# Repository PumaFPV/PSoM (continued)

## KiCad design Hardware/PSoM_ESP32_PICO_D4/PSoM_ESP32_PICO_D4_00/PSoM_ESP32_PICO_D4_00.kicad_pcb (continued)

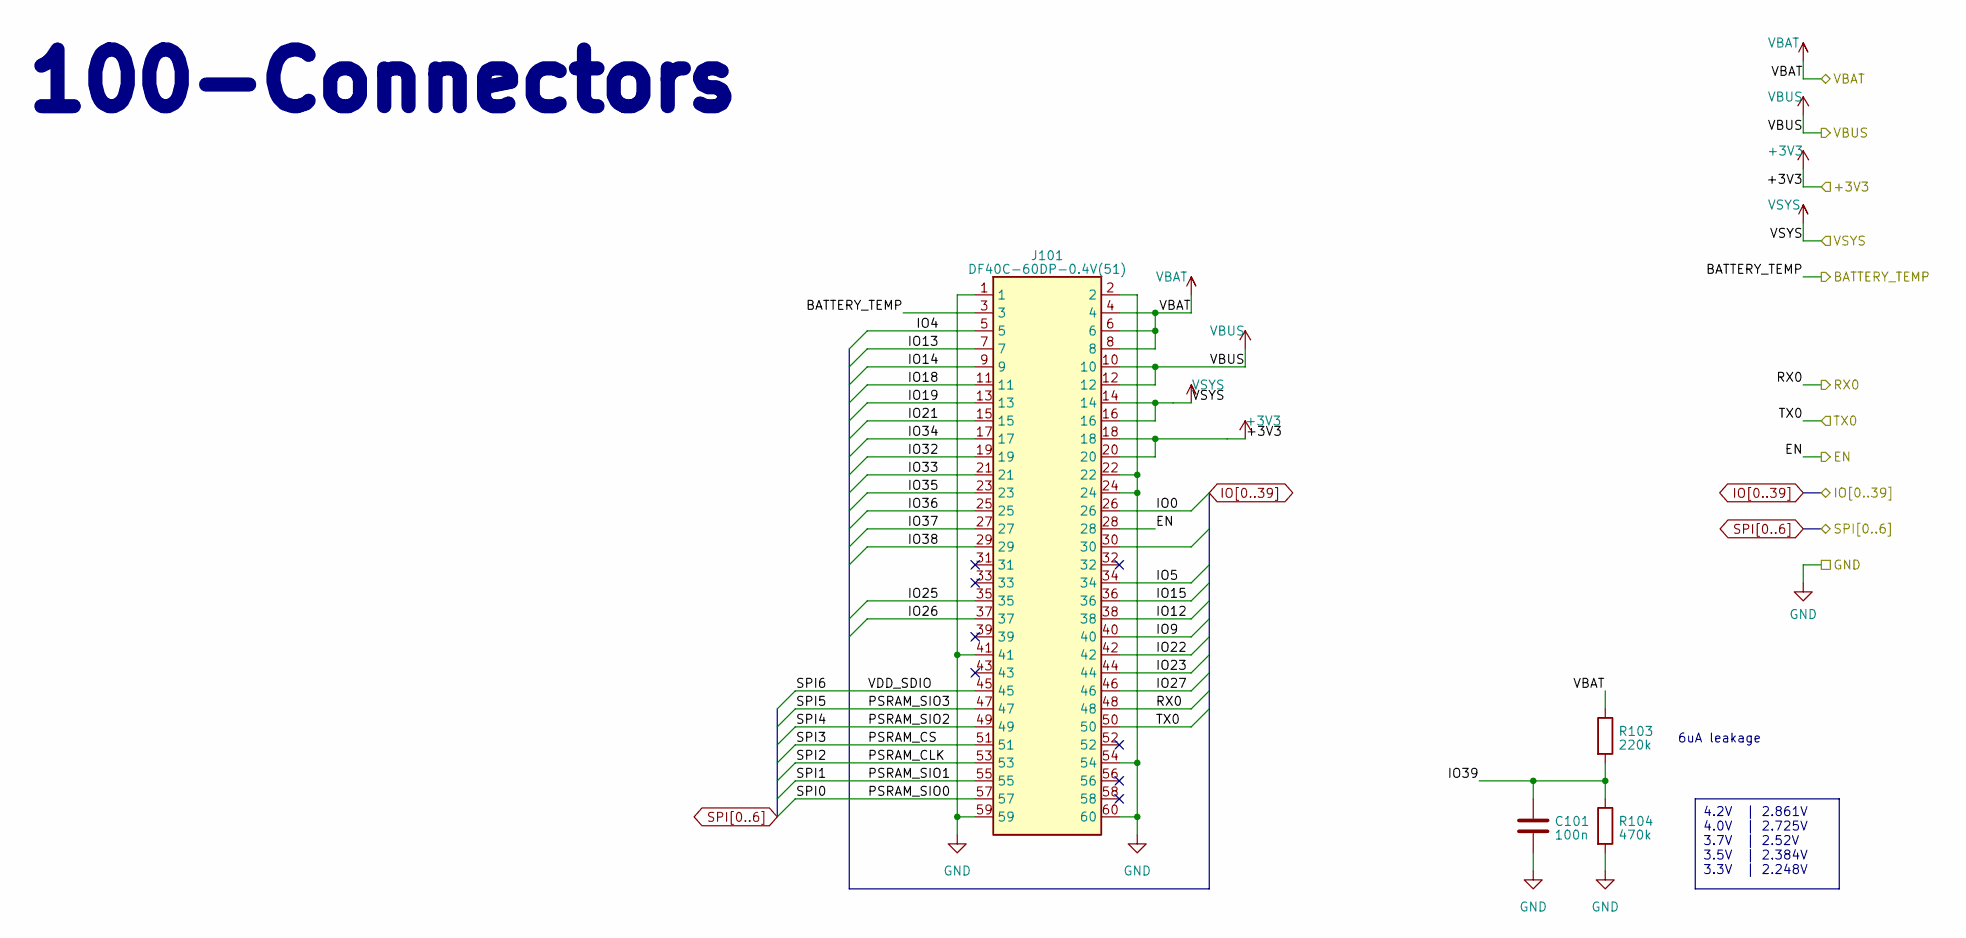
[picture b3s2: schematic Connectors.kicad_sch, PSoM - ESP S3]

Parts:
C101: 100n; C_0201_0603Metric
J101: DF40C-60DP-0.4V(51)
R103: 220k; R_0201_0603Metric
R104: 470k; R_0201_0603Metric

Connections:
+3V3: J101.18, J101.20; also elsewhere on the board
/100_Connectors/BATTERY_TEMP: J101.3; also elsewhere on the board
/100_Connectors/EN: J101.28; also elsewhere on the board
/100_Connectors/RX0: J101.48; also elsewhere on the board
/100_Connectors/TX0: J101.50; also elsewhere on the board
/VBAT: J101.4, J101.6, J101.8, R103.1; also elsewhere on the board
/VSYS: J101.14, J101.16; also elsewhere on the board
GND: C101.2, J101.1, J101.2, J101.22, J101.24, J101.41, J101.54, J101.59, J101.60, R104.2; also elsewhere on the board
IO0: J101.26; also elsewhere on the board
IO4: J101.5; also elsewhere on the board
IO5: J101.34; also elsewhere on the board
IO9: J101.40; also elsewhere on the board
IO12: J101.38; also elsewhere on the board
IO13: J101.7; also elsewhere on the board
IO14: J101.9; also elsewhere on the board
IO15: J101.36; also elsewhere on the board
IO18: J101.11; also elsewhere on the board
IO19: J101.13; also elsewhere on the board
IO21: J101.15; also elsewhere on the board
IO22: J101.42; also elsewhere on the board
IO23: J101.44; also elsewhere on the board
IO25: J101.35; also elsewhere on the board
IO26: J101.37; also elsewhere on the board
IO27: J101.46; also elsewhere on the board
IO32: J101.19; also elsewhere on the board
IO33: J101.21; also elsewhere on the board
IO34: J101.17; also elsewhere on the board
IO35: J101.23; also elsewhere on the board
IO36: J101.25; also elsewhere on the board
IO37: J101.27; also elsewhere on the board
IO38: J101.29; also elsewhere on the board
IO39: C101.1, R103.2, R104.1; also elsewhere on the board
SPI0: J101.57; also elsewhere on the board
SPI1: J101.55; also elsewhere on the board
SPI2: J101.53; also elsewhere on the board
SPI3: J101.51; also elsewhere on the board
SPI4: J101.49; also elsewhere on the board
SPI5: J101.47; also elsewhere on the board
SPI6: J101.45; also elsewhere on the board
VBUS: J101.10, J101.12; also elsewhere on the board

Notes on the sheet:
4.2V | 2.861V 4.0V | 2.725V 3.7V | 2.52V 3.5V | 2.384V 3.3V | 2.248V
100-Connectors
6uA leakage

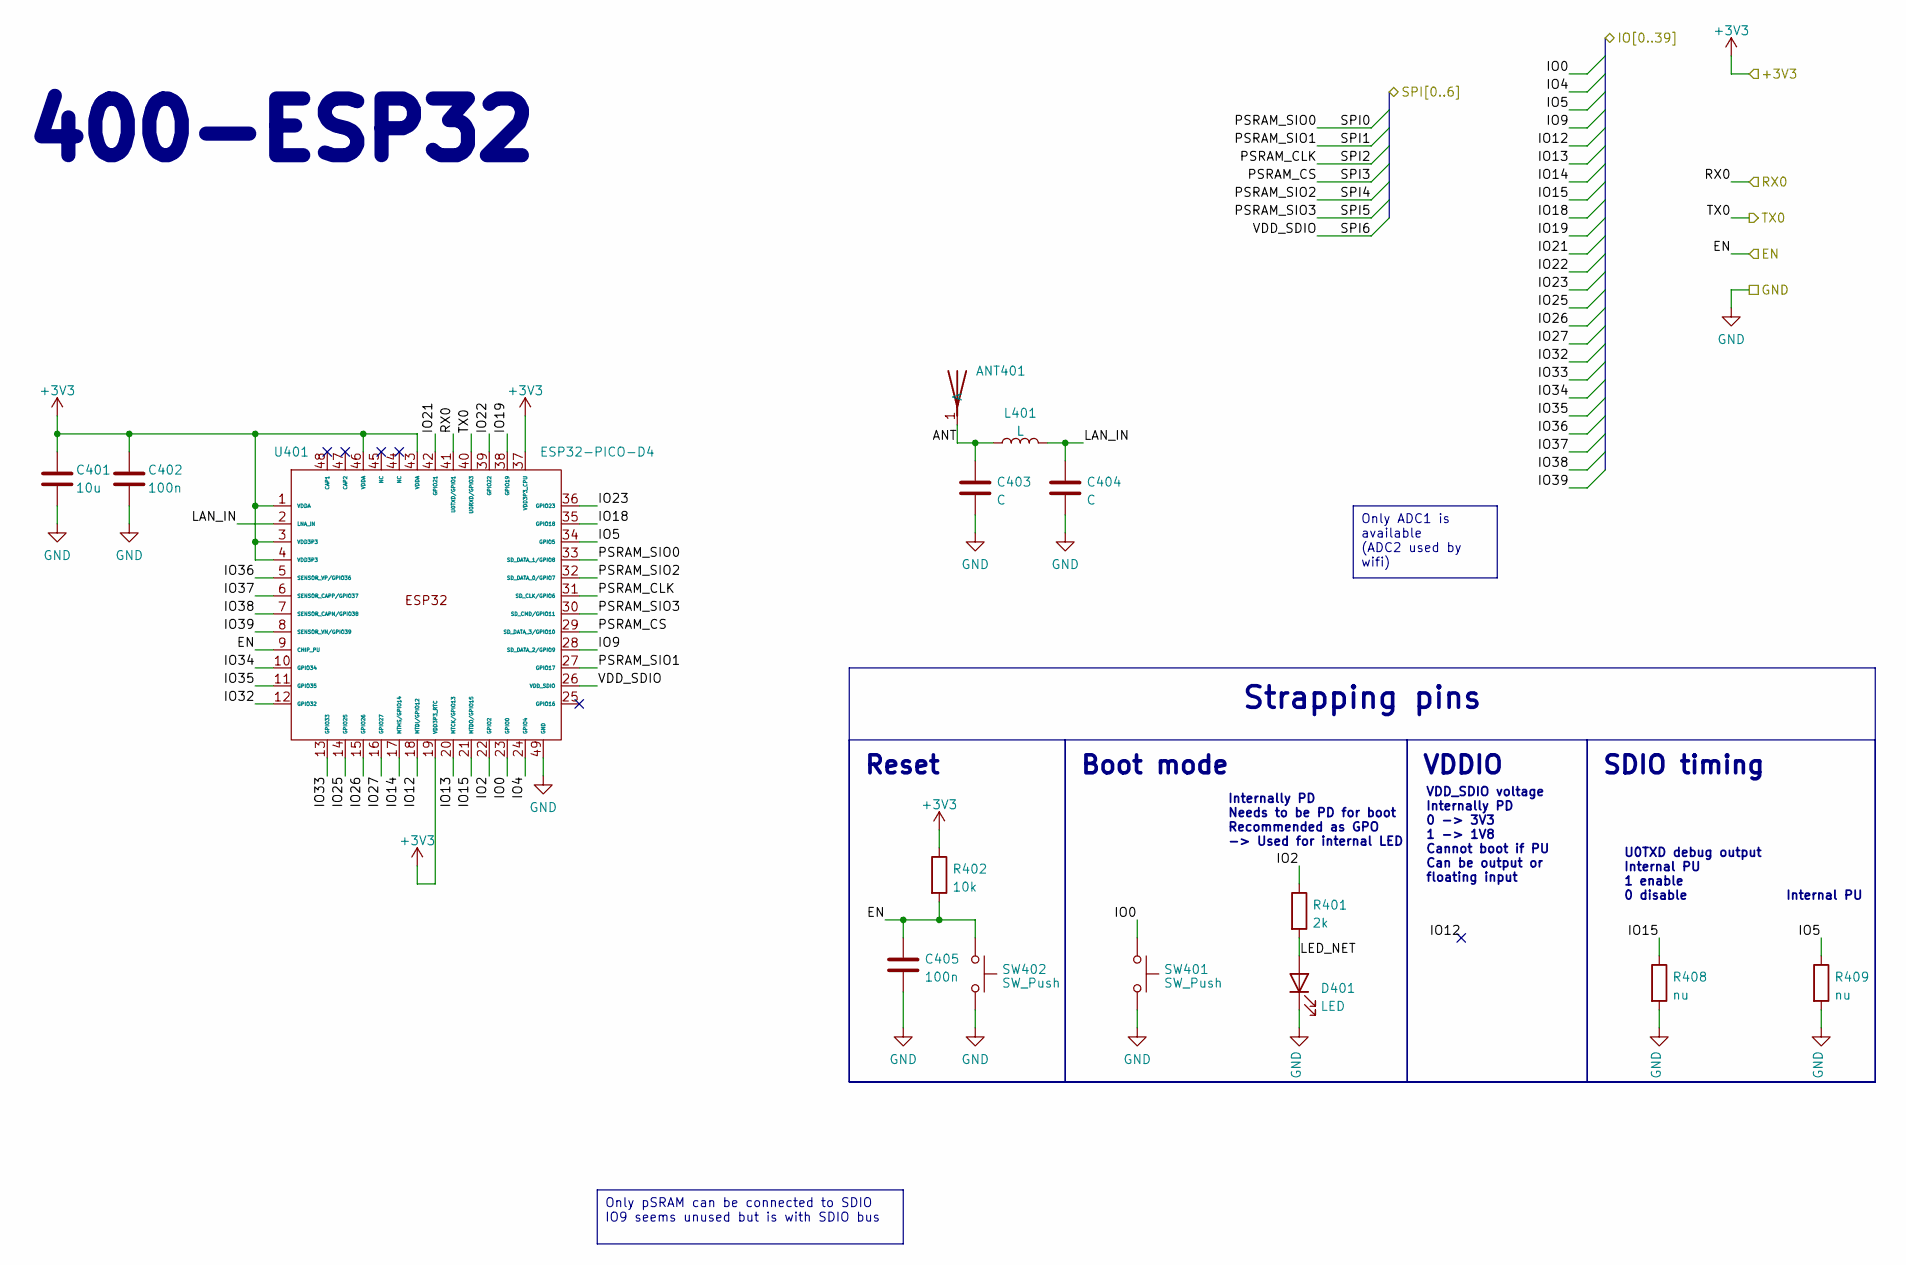
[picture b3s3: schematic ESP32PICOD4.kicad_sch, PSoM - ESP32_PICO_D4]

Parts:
ANT401: 2450AT18A100E; ANTC3216X140N; Mouser Part Number 609-2450AT18A100E
C401: 10u; C_0603_1608Metric
C402, C405: 100n; C_0201_0603Metric
C403, C404: C; C_0201_0603Metric
D401: LED; LED_0402_1005Metric
L401: L; L_0201_0603Metric
R401: 2k; R_0402_1005Metric
R402: 10k; R_0201_0603Metric
R408, R409: nu; R_0201_0603Metric
SW401, SW402: SW_Push; B3U-1000P
U401: ESP32-PICO-D4; ESP32-PICO-D4_1; Mouser Part Number 356-ESP32-PICO-D4

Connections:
+3V3: C401.1, C402.1, R402.1, U401.1 (VDDA), U401.3 (VDD3P3), U401.4 (VDD3P3), U401.19 (VDD3P3_RTC), U401.37 (VDD3P3_CPU), U401.43 (VDDA), U401.46 (VDDA); also elsewhere on the board
/100_Connectors/EN: C405.1, R402.2, SW402.1, U401.9 (CHIP_PU); also elsewhere on the board
/100_Connectors/RX0: U401.41 (U0TXD/GPIO1); also elsewhere on the board
/100_Connectors/TX0: U401.40 (U0RXD/GPIO3); also elsewhere on the board
/400_ESP32/ANT: ANT401.1 (A), C403.1, L401.1
/400_ESP32/LAN_IN: C404.1, L401.2, U401.2 (LNA_IN)
/400_ESP32/LED_NET: D401.2 (A), R401.2
GND: C401.2, C402.2, C403.2, C404.2, C405.2, D401.1 (K), R408.2, R409.2, SW401.2, SW402.2, U401.49 (GND); also elsewhere on the board
IO0: SW401.1, U401.23 (GPIO0); also elsewhere on the board
IO2: R401.1, U401.22 (GPIO2)
IO4: U401.24 (GPIO4); also elsewhere on the board
IO5: R409.1, U401.34 (GPIO5); also elsewhere on the board
IO9: U401.28 (SD_DATA_2/GPIO9); also elsewhere on the board
IO12: U401.18 (MTDI/GPIO12); also elsewhere on the board
IO13: U401.20 (MTCK/GPIO13); also elsewhere on the board
IO14: U401.17 (MTMS/GPIO14); also elsewhere on the board
IO15: R408.1, U401.21 (MTDO/GPIO15); also elsewhere on the board
IO18: U401.35 (GPIO18); also elsewhere on the board
IO19: U401.38 (GPIO19); also elsewhere on the board
IO21: U401.42 (GPIO21); also elsewhere on the board
IO22: U401.39 (GPIO22); also elsewhere on the board
IO23: U401.36 (GPIO23); also elsewhere on the board
IO25: U401.14 (GPIO25); also elsewhere on the board
IO26: U401.15 (GPIO26); also elsewhere on the board
IO27: U401.16 (GPIO27); also elsewhere on the board
IO32: U401.12 (GPIO32); also elsewhere on the board
IO33: U401.13 (GPIO33); also elsewhere on the board
IO34: U401.10 (GPIO34); also elsewhere on the board
IO35: U401.11 (GPIO35); also elsewhere on the board
IO36: U401.5 (SENSOR_VP/GPIO36); also elsewhere on the board
IO37: U401.6 (SENSOR_CAPP/GPIO37); also elsewhere on the board
IO38: U401.7 (SENSOR_CAPN/GPIO38); also elsewhere on the board
IO39: U401.8 (SENSOR_VN/GPIO39); also elsewhere on the board
SPI0: U401.33 (SD_DATA_1/GPIO8); also elsewhere on the board
SPI1: U401.27 (GPIO17); also elsewhere on the board
SPI2: U401.31 (SD_CLK/GPIO6); also elsewhere on the board
SPI3: U401.29 (SD_DATA_3/GPIO10); also elsewhere on the board
SPI4: U401.32 (SD_DATA_0/GPIO7); also elsewhere on the board
SPI5: U401.30 (SD_CMD/GPIO11); also elsewhere on the board
SPI6: U401.26 (VDD_SDIO); also elsewhere on the board

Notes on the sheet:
Only pSRAM can be connected to SDIO IO9 seems unused but is with SDIO bus
Reset
SDIO timing
VDDIO
Boot mode
Strapping pins
Only ADC1 is available (ADC2 used by wifi)
Internally PD Needs to be PD for boot Recommended as GPO -> Used for internal LED
Internal PU
400-ESP32
VDD_SDIO voltage Internally PD 0 -> 3V3 1 -> 1V8 Cannot boot if PU Can be output or floating input
U0TXD debug output Internal PU 1 enable 0 disable

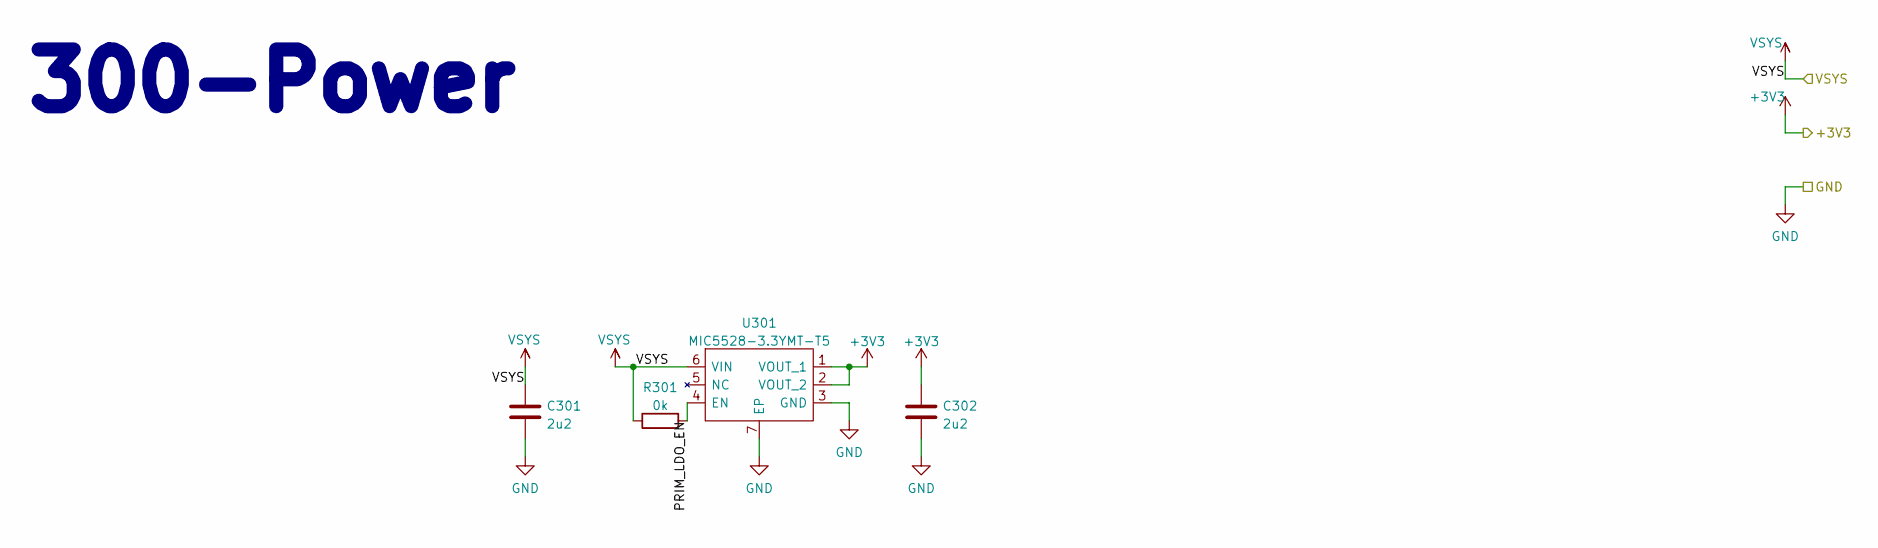
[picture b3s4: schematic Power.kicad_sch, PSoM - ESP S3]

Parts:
C301, C302: 2u2; C_0603_1608Metric
R301: 0k; R_0201_0603Metric
U301: MIC5528-3.3YMT-T5; SON40P120X120X60-7N-D; Mouser Part Number 998-MIC5528-3.3YMTT5

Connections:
+3V3: C302.1, U301.1 (VOUT_1), U301.2 (VOUT_2); also elsewhere on the board
/300_Power/PRIM_LDO_EN: R301.2, U301.4 (EN)
/VSYS: C301.1, R301.1, U301.6 (VIN); also elsewhere on the board
GND: C301.2, C302.2, U301.3 (GND), U301.7 (EP); also elsewhere on the board

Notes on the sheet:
300-Power

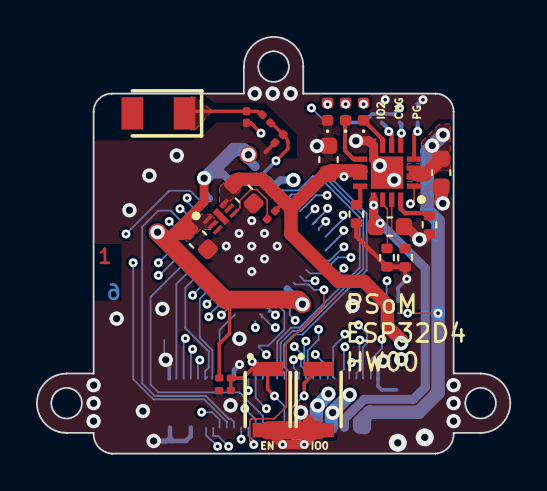
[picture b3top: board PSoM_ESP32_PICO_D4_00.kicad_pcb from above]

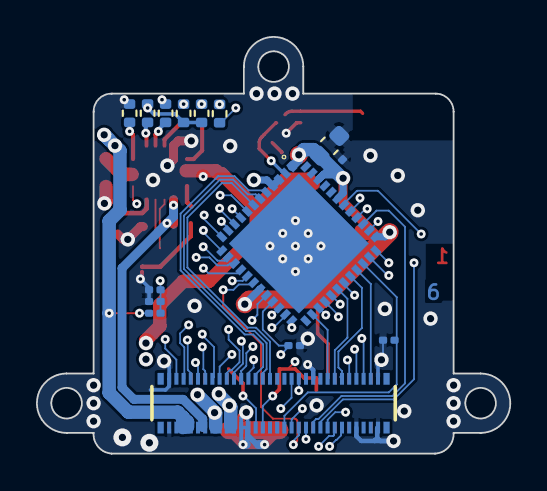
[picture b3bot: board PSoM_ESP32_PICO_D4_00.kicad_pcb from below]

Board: 6 copper layers, 26.3 x 23.2 mm, 38 parts (15 on the bottom side), 56 nets.

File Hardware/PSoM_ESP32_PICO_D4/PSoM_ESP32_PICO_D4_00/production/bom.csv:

Designator,Footprint,Quantity,Value,LCSC Part #
ANT401,ANTC3216X140N,1,2450AT18A100E,
"C101, C402, C405",0201,3,100n,
"C201, C203",0603,2,4u7,
C202,0603,1,1u,
"C301, C302",0603,2,2u2,
C401,0603,1,10u,
"C403, C404",0201,2,C,
"D201, D202, D401",0402,3,LED,
J101,DF40C-60DP-0.4V(51),1,DF40C-60DP-0.4V(51),
L401,0201,1,L,
"R1, R2",0402,2,R,
R103,0201,1,220k,
R104,0201,1,470k,
R201,0402,1,0,
R202,0402,1,36k5,
R203,0402,1,590,
R204,0402,1,1k1,
"R205, R206",0402,2,1k5,
R207,0402,1,100k,
R301,0201,1,0k,
R401,0402,1,2k,
R402,0201,1,10k,
"R408, R409",0201,2,nu,
"SW401, SW402",B3U-1000P,2,SW_Push,
U201,QFN50P300X300X100-17N-D,1,BQ24075RGTR,
U301,SON40P120X120X60-7N-D,1,MIC5528-3.3YMT-T5,
U401,ESP32-PICO-D4_1,1,ESP32-PICO-D4,

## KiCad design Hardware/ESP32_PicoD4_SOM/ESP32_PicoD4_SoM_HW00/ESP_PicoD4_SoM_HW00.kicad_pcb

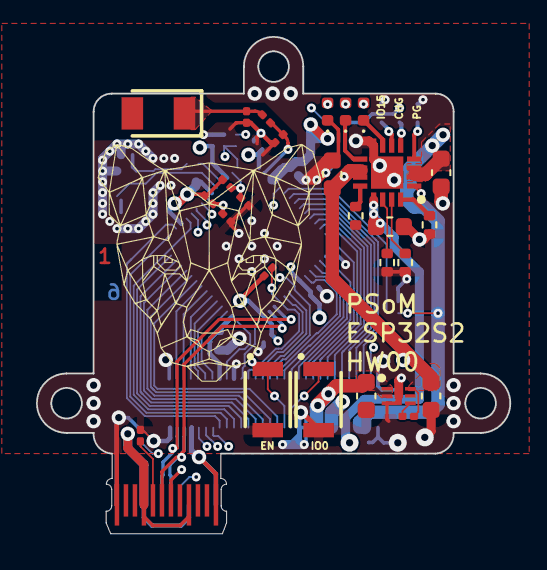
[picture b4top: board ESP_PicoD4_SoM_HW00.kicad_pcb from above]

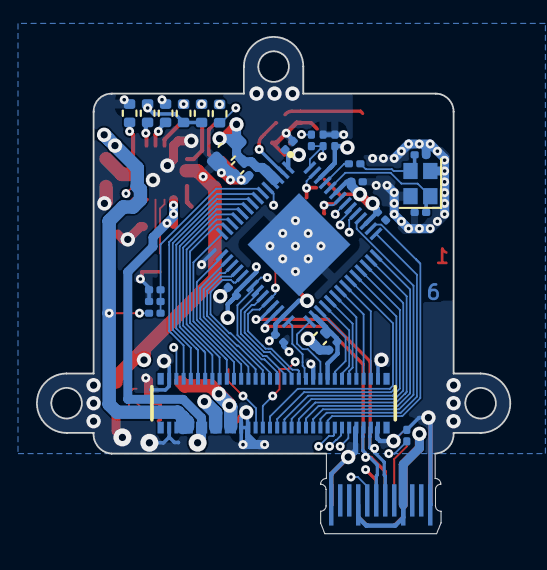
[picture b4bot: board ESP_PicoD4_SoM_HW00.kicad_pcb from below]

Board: 6 copper layers, 26.3 x 27.6 mm, 57 parts (29 on the bottom side), 71 nets.

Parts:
ANT401: 2450AT18A100E; ANTC3216X140N
C101, C403, C404, C405, C408, C411, C412, C414, C415, C416: 100n; C_0201_0603Metric
C201, C203: 4u7; C_0603_1608Metric
C202: 1u; C_0603_1608Metric
C301, C302: 2u2; C_0603_1608Metric
C401, C402: 15p; C_0201_0603Metric
C406, C407: C; C_0201_0603Metric
C409: 10u; C_0603_1608Metric
C410, C413: 1u; C_0402_1005Metric
D201, D202, D401: LED; LED_0402_1005Metric
J101: DF40C-60DP-0.4V(51)
J102: Bare PCB USB C; usb-c-pcb
L401: L; L_0201_0603Metric
R1, R2: R; R_0402_1005Metric
R101, R102: 5.1k; R_0201_0603Metric
R103: 220k; R_0201_0603Metric
R104: 470k; R_0201_0603Metric
R201: 0; R_0402_1005Metric
R202: 36k5; R_0402_1005Metric
R203: 590; R_0402_1005Metric
R204: 1k1; R_0402_1005Metric
R205, R206: 1k5; R_0402_1005Metric
R207: 100k; R_0402_1005Metric
R301: 0k; R_0201_0603Metric
R401: 0; R_0201_0603Metric
R402: 2k; R_0402_1005Metric
R403, R404: 10k; R_0201_0603Metric
R405, R406, R407, R408: nu; R_0201_0603Metric
SW401, SW402: SW_Push; B3U-1000P
U201: BQ24075RGTR; QFN50P300X300X100-17N-D
U301: MIC5528-3.3YMT-T5; SON40P120X120X60-7N-D
U401: ESP32-S2FH4; QFN40P700X700X90-57N-D
Y601: Crystal_GND24_Small; Crystal_SMD_2016-4Pin_2.0x1.6mm

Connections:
+3V3: C302.1, C403.1, C404.1, C405.1, C408.1, C409.1, C410.1, C411.1, C415.1, C416.1, J101.18, J101.20, R403.1, R404.1, R405.1, R406.1, U301.1 (VOUT_1), U301.2 (VOUT_2), U401.1 (VDDA_1), U401.3 (VDD3P3_1), U401.4 (VDD3P3_2), U401.20 (VDD3P3_RTC), U401.27 (VDD3P3_RTC_IO), U401.45 (VDD3P3_CPU), U401.51 (VDDA_2), U401.54 (VDDA_3)
/100_Connectors/BATTERY_TEMP: J101.3, U201.1 (TS)
/100_Connectors/CC1: J102.A5 (CC1), R102.1
/100_Connectors/CC2: J102.B5 (CC2), R101.1
/100_Connectors/D+: J101.56, J102.A6 (D+), J102.B6 (D+), U401.26 (GPIO20)
/100_Connectors/D-: J101.58, J102.A7 (D-), J102.B7 (D-), U401.25 (GPIO19)
/100_Connectors/EN: C414.1, J101.28, R403.2, SW401.1, U401.56 (CHIP_PU)
/100_Connectors/RX0: J101.48, U401.49 (U0RXD)
/100_Connectors/TX0: J101.50, U401.48 (U0TXD)
/200_1S_Charger/BQ_CE: R207.1, U201.4 (~CE)
/200_1S_Charger/BQ_CHG: D202.1 (K), U201.9 (~CHG)
/200_1S_Charger/BQ_PGOOD: D201.1 (K), U201.7 (~PGOOD)
/200_1S_Charger/EN1: R1.1, U201.6 (EN1)
/200_1S_Charger/EN2: R2.1, U201.5 (EN2)
/200_1S_Charger/ILIM: R204.2, U201.12 (ILIM)
/200_1S_Charger/ISET: R203.1, U201.16 (ISET)
/200_1S_Charger/LED_CHG: D202.2 (A), R206.2
/200_1S_Charger/LED_PG: D201.2 (A), R205.2
/200_1S_Charger/SYSOFF: R201.1, U201.15 (SYSOFF)
/200_1S_Charger/TMR: R202.1, U201.14 (TMR)
/300_Power/PRIM_LDO_EN: R301.2, U301.4 (EN)
/400_ESP32/ANT: ANT401.1 (A), C406.1, L401.1
/400_ESP32/IO45: R406.2, R408.1, U401.50 (GPIO45)
/400_ESP32/IO46: R405.2, R407.1, U401.55 (GPIO46)
/400_ESP32/LED_NET: D401.2 (A), R402.2
/400_ESP32/LNA_IN: C407.1, L401.2, U401.2 (LNA_IN)
/VBAT: C201.1, J101.4, J101.6, J101.8, R103.1, U201.2 (BAT_1), U201.3 (BAT_2)
/VSYS: C203.1, C301.1, J101.14, J101.16, R2.2, R205.1, R206.1, R301.1, U201.10 (OUT_1), U201.11 (OUT_2), U301.6 (VIN)
GND: C101.2, C201.2, C202.2, C203.2, C301.2, C302.2, C401.2, C402.2, C403.2, C404.2, C405.2, C406.2, C407.2, C408.2, C409.2, C410.2, C411.2, C412.2, C413.2, C414.2, C415.2, C416.2, D401.1 (K), J101.1, J101.2, J101.22, J101.24, J101.41, J101.54, J101.59, J101.60, J102.A1 (GND), J102.A12 (GND), J102.B1 (GND), J102.B12 (GND), R1.2, R101.2, R102.2, R104.2, R201.2, R202.2, R203.2, R204.1, R207.2, R407.2, R408.2, SW401.2, SW402.2, U201.8 (VSS), U201.17 (GND), U301.3 (GND), U301.7 (EP), U401.57 (GND), Y601.2, Y601.4
IO0: J101.26, SW402.1, U401.5 (GPIO0)
IO1: C101.1, R103.2, R104.1, U401.6 (GPIO1)
IO2: J101.5, U401.7 (GPIO2)
IO3: J101.7, U401.8 (GPIO3)
IO4: J101.9, U401.9 (GPIO4)
IO5: J101.11, U401.10 (GPIO5)
IO6: J101.13, U401.11 (GPIO6)
IO7: J101.15, U401.12 (GPIO7)
IO8: J101.17, U401.13 (GPIO8)
IO9: J101.19, U401.14 (GPIO9)
IO10: J101.21, U401.15 (GPIO10)
IO11: J101.23, U401.16 (GPIO11)
IO12: J101.25, U401.17 (GPIO12)
IO13: J101.27, U401.18 (GPIO13)
IO14: J101.29, U401.19 (GPIO14)
IO15: J101.31, R402.1, U401.21 (XTAL_32K_P)
IO16: J101.33, U401.22 (XTAL_32K_N)
IO17: J101.35, U401.23 (DAC_1)
IO18: J101.37, R404.2, U401.24 (DAC_2)
IO21: J101.39, U401.28 (GPIO21)
IO33: J101.30, U401.37 (GPIO33)
IO34: J101.32, U401.38 (GPIO34)
IO35: J101.34, U401.39 (GPIO35)
IO36: J101.36, U401.40 (GPIO36)
IO37: J101.38, U401.41 (GPIO37)
IO38: J101.40, U401.42 (GPIO38)
IO39: J101.44, U401.43 (MTCK)
IO40: J101.46, U401.44 (MTD0)
IO41: J101.42, U401.46 (MTDI)
IO42: J101.52, U401.47 (MTMS)
unnamed: C401.1, R401.1, Y601.3
unnamed: C402.1, U401.52 (XTAL_N), Y601.1
unnamed: R401.2, U401.53 (XTAL_P)
SPI0: J101.57, U401.36 (SPID)
SPI1: J101.55, U401.35 (SPIQ)
SPI2: J101.53, U401.34 (SPICLK)
SPI3: J101.51, U401.33 (SPICS0)
SPI4: J101.49, U401.32 (SPIWP)
SPI5: J101.47, U401.31 (SPIHD)
SPI6: C412.1, C413.1, J101.45, U401.30 (VDD_SPI)
SPI7: J101.43, U401.29 (SPICS1)
VBUS: C202.1, J101.10, J101.12, J102.A4 (VBUS), J102.A9 (VBUS), J102.B4 (VBUS), J102.B9 (VBUS), U201.13 (IN)

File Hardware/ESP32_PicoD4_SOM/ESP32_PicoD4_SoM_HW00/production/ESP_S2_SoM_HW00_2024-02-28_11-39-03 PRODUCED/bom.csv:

Designator,Footprint,Quantity,Value,LCSC Part #
ANT401,ANTC3216X140N,1,2450AT18A100E,
"C101, C403, C404, C405, C408, C411, C412, C414, C415, C416",0201,10,100n,
"C201, C203",0603,2,4u7,
C202,0603,1,1u,
"C301, C302",0603,2,2u2,
"C401, C402",0201,2,15p,
"C406, C407",0201,2,C,
C409,0603,1,10u,
"C410, C413",0402,2,1u,
"D201, D202, D401",0402,3,LED,
J101,DF40C-60DP-0.4V(51),1,DF40C-60DP-0.4V(51),
J102,usb-c-pcb,1,Bare PCB USB C,
L401,0201,1,L,
"R1, R2",0402,2,R,
"R101, R102",0201,2,5.1k,
R103,0201,1,220k,
R104,0201,1,470k,
R201,0402,1,0,
R202,0402,1,36k5,
R203,0402,1,590,
R204,0402,1,1k1,
"R205, R206",0402,2,1k5,
R207,0402,1,100k,
R301,0201,1,0k,
R401,0201,1,0,
R402,0402,1,2k,
"R403, R404",0201,2,10k,
"R405, R406, R407, R408",0201,4,nu,
"SW401, SW402",B3U-1000P,2,SW_Push,
U201,QFN50P300X300X100-17N-D,1,BQ24075RGTR,
U301,SON40P120X120X60-7N-D,1,MIC5528-3.3YMT-T5,
U401,QFN40P700X700X90-57N-D,1,ESP32-S2FH4,
Y601,Crystal_SMD_2016-4Pin_2.0x1.6mm,1,Crystal_GND24_Small,

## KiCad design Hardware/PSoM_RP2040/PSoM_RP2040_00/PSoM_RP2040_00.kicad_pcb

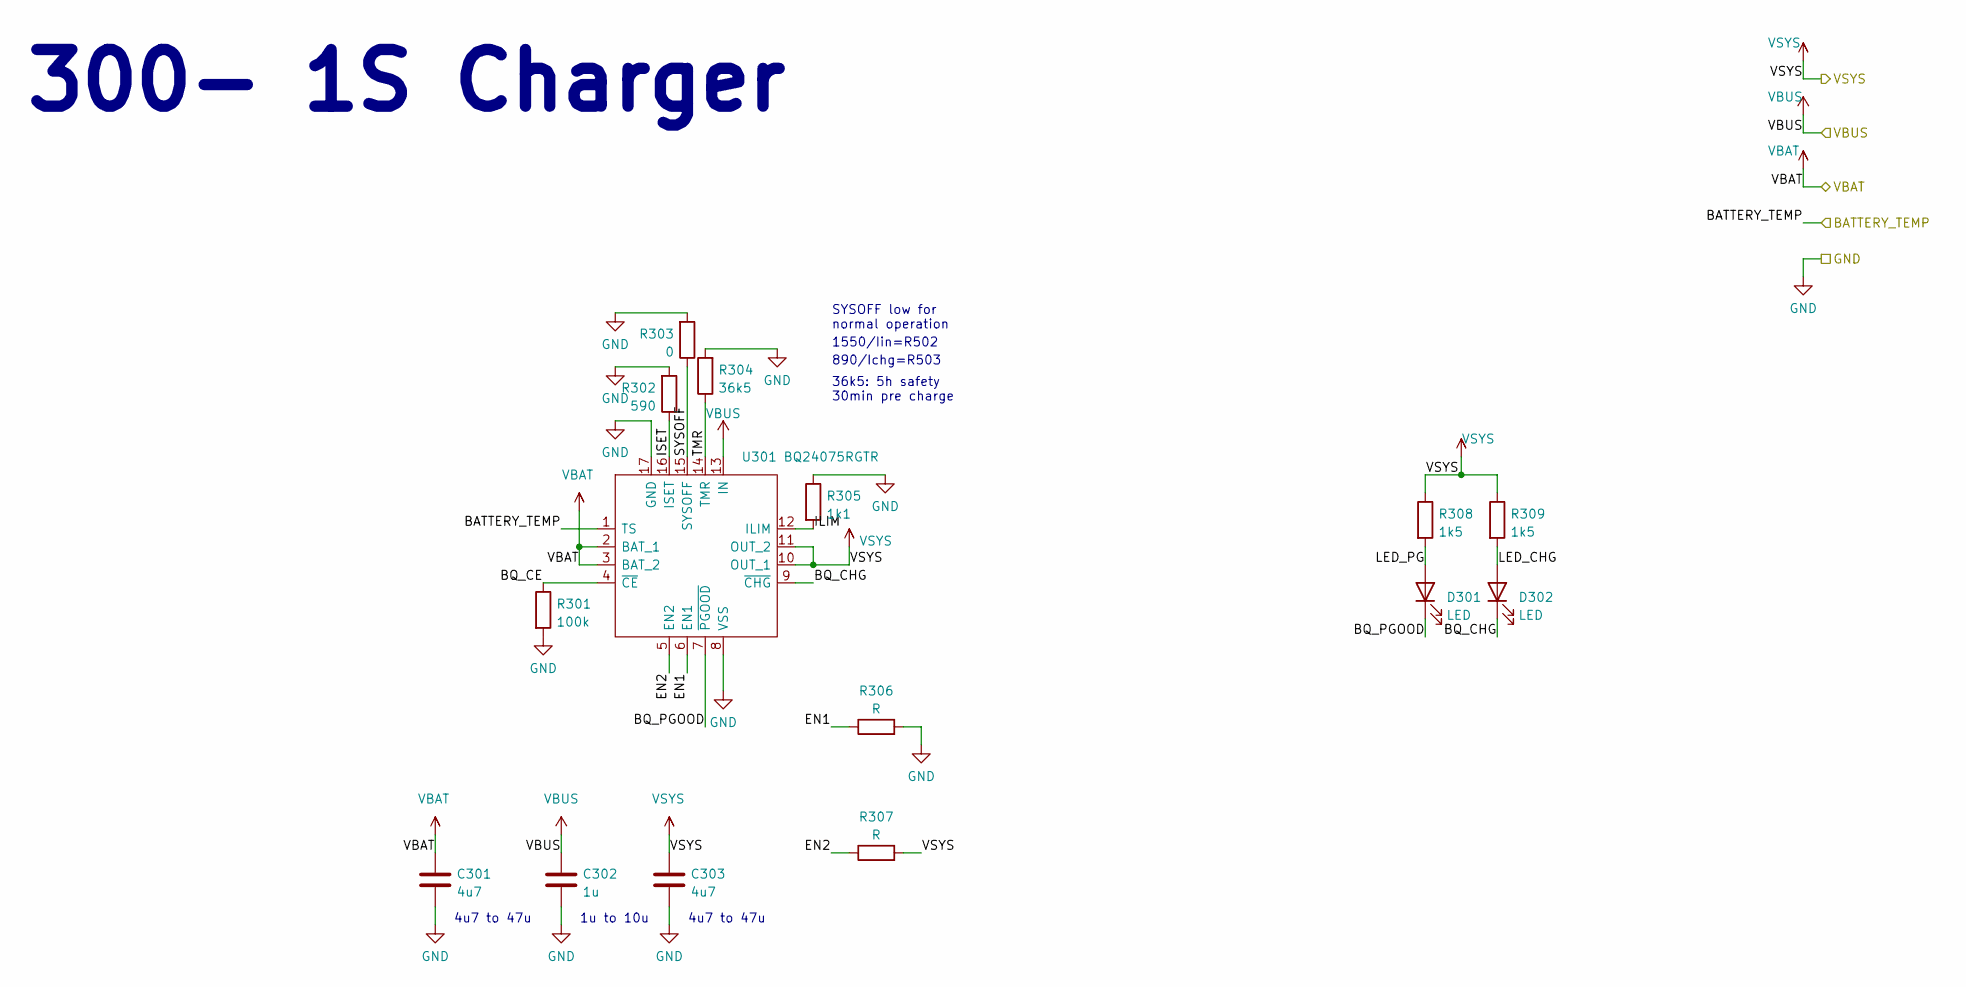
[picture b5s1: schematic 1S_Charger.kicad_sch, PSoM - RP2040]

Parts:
C301, C303: 4u7; C_0603_1608Metric
C302: 1u; C_0603_1608Metric
D301, D302: LED; LED_0402_1005Metric
R301: 100k; R_0402_1005Metric
R302: 590; R_0402_1005Metric
R303: 0; R_0402_1005Metric
R304: 36k5; R_0402_1005Metric
R305: 1k1; R_0402_1005Metric
R306, R307: R; R_0402_1005Metric
R308, R309: 1k5; R_0402_1005Metric
U301: BQ24075RGTR; QFN50P300X300X100-17N-D; Mouser Part Number 595-BQ24075RGTR

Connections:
/200_Connectors/BATTERY_TEMP: U301.1 (TS); also elsewhere on the board
/300_1S_Charger/BQ_CE: R301.1, U301.4 (~CE)
/300_1S_Charger/BQ_CHG: D302.1 (K), U301.9 (~CHG)
/300_1S_Charger/BQ_PGOOD: D301.1 (K), U301.7 (~PGOOD)
/300_1S_Charger/EN1: R306.1, U301.6 (EN1)
/300_1S_Charger/EN2: R307.1, U301.5 (EN2)
/300_1S_Charger/ILIM: R305.2, U301.12 (ILIM)
/300_1S_Charger/ISET: R302.1, U301.16 (ISET)
/300_1S_Charger/LED_CHG: D302.2 (A), R309.2
/300_1S_Charger/LED_PG: D301.2 (A), R308.2
/300_1S_Charger/SYSOFF: R303.1, U301.15 (SYSOFF)
/300_1S_Charger/TMR: R304.1, U301.14 (TMR)
/VBAT: C301.1, U301.2 (BAT_1), U301.3 (BAT_2); also elsewhere on the board
/VSYS: C303.1, R307.2, R308.1, R309.1, U301.10 (OUT_1), U301.11 (OUT_2); also elsewhere on the board
VBUS: C302.1, U301.13 (IN); also elsewhere on the board

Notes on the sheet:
890/Ichg=R503
300- 1S Charger
4u7 to 47u
1u to 10u
SYSOFF low for normal operation
36k5: 5h safety 30min pre charge
1550/Iin=R502

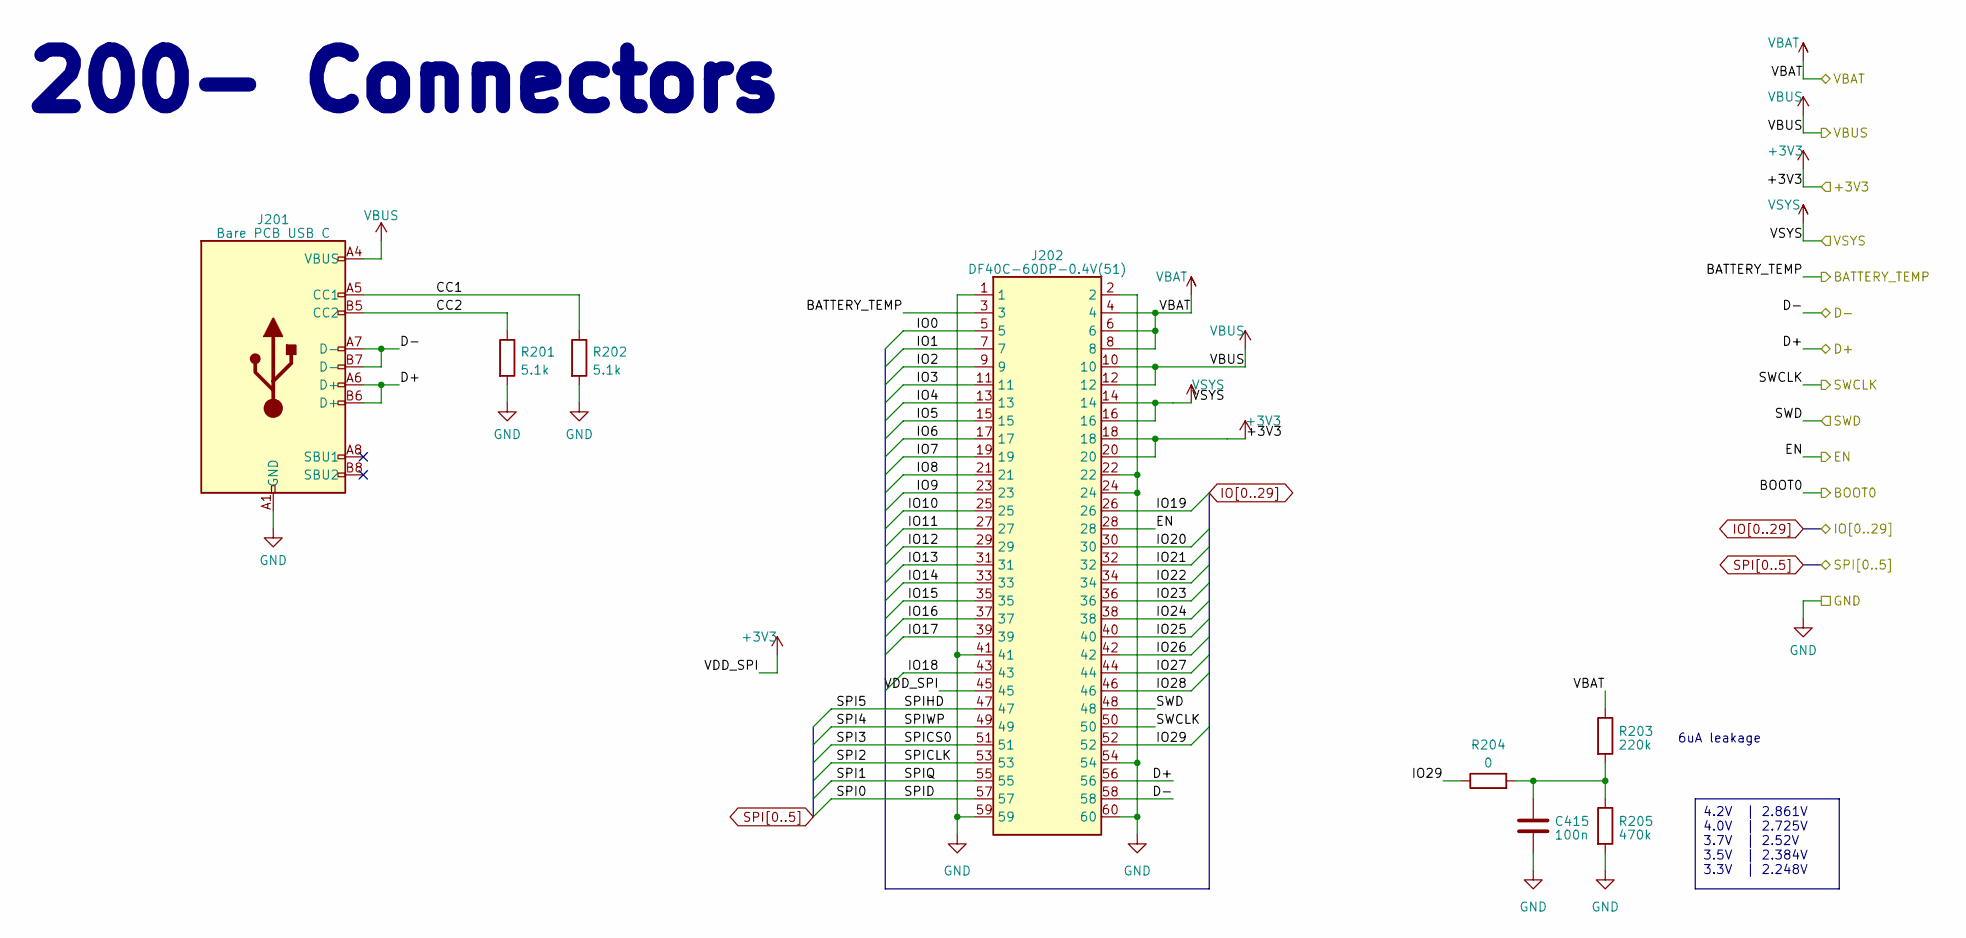
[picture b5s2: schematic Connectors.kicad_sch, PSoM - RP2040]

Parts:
C415: 100n; C_0201_0603Metric
J201: Bare PCB USB C; usb-c-pcb; Mouser Part Number 640-USB4510031A
J202: DF40C-60DP-0.4V(51)
R201, R202: 5.1k; R_0201_0603Metric
R203: 220k; R_0201_0603Metric
R204: 0; R_0201_0603Metric
R205: 470k; R_0201_0603Metric

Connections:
+3V3: J202.18, J202.20, J202.45; also elsewhere on the board
/200_Connectors/BATTERY_TEMP: J202.3; also elsewhere on the board
/200_Connectors/CC1: J201.A5 (CC1), R202.1
/200_Connectors/CC2: J201.B5 (CC2), R201.1
/200_Connectors/D+: J201.A6 (D+), J201.B6 (D+), J202.56; also elsewhere on the board
/200_Connectors/D-: J201.A7 (D-), J201.B7 (D-), J202.58; also elsewhere on the board
/200_Connectors/EN: J202.28; also elsewhere on the board
/200_Connectors/SWCLK: J202.50; also elsewhere on the board
/200_Connectors/SWD: J202.48; also elsewhere on the board
/VBAT: J202.4, J202.6, J202.8, R203.1; also elsewhere on the board
/VSYS: J202.14, J202.16; also elsewhere on the board
IO0: J202.5; also elsewhere on the board
IO1: J202.7; also elsewhere on the board
IO2: J202.9; also elsewhere on the board
IO3: J202.11; also elsewhere on the board
IO4: J202.13; also elsewhere on the board
IO5: J202.15; also elsewhere on the board
IO6: J202.17; also elsewhere on the board
IO7: J202.19; also elsewhere on the board
IO8: J202.21; also elsewhere on the board
IO9: J202.23; also elsewhere on the board
IO10: J202.25; also elsewhere on the board
IO11: J202.27; also elsewhere on the board
IO12: J202.29; also elsewhere on the board
IO13: J202.31; also elsewhere on the board
IO14: J202.33; also elsewhere on the board
IO15: J202.35; also elsewhere on the board
IO16: J202.37; also elsewhere on the board
IO17: J202.39; also elsewhere on the board
IO18: J202.43; also elsewhere on the board
IO19: J202.26; also elsewhere on the board
IO20: J202.30; also elsewhere on the board
IO21: J202.32; also elsewhere on the board
IO22: J202.34; also elsewhere on the board
IO23: J202.36; also elsewhere on the board
IO24: J202.38; also elsewhere on the board
IO25: J202.40; also elsewhere on the board
IO26: J202.42; also elsewhere on the board
IO27: J202.44; also elsewhere on the board
IO28: J202.46; also elsewhere on the board
SPI0: J202.57; also elsewhere on the board
SPI1: J202.55; also elsewhere on the board
SPI2: J202.53; also elsewhere on the board
SPI3: J202.51; also elsewhere on the board
SPI4: J202.49; also elsewhere on the board
SPI5: J202.47; also elsewhere on the board
VBUS: J201.A4 (VBUS), J201.A9 (VBUS), J201.B4 (VBUS), J201.B9 (VBUS), J202.10, J202.12; also elsewhere on the board

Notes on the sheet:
4.2V | 2.861V 4.0V | 2.725V 3.7V | 2.52V 3.5V | 2.384V 3.3V | 2.248V
200- Connectors
6uA leakage
